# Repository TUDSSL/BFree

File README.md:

# BFree

This is the official public repository for a **battery-free** prototyping platform with [CircuitPython](https://circuitpython.org/) for the [Adafruit Metro M0 Express](https://www.adafruit.com/product/3505). This repository contains all the sources needed to get started using CircuitPython without any batteries!

## Project Overview

### Rationale
Batteries are bad for the environment, and many embedded applications do not rely on a constant flow of energy. However, just connecting an energy-harvesting source to a microcontroller does not fully solve the problem. Energy from harvested sources is not constant and maybe not enough to continuously run the device, so we have to buffer some energy (typically in a capacitor). When a certain amount of energy is collected, the system activates for some seconds.

It would be problematic if the program would start from the beginning every time the system restarts. Going into a sleep mode might also be problematic, as you never know when the energy returns.

**This work focuses on continuing a Python application where it left off when the system restarts after a power failure, called intermittent-computing**
We achieve this without any involvement from the user or any modifications to the Python code!

All the magic happens internally in our modified version of the CircuitPython interpreter ([added as a submodule in software/BFree-core](https://github.com/TUDSSL/BFree-core)), which works together with our [BFree shield](hardware/BFree-shield). Everything is entirely open-source and accessible through this GitHub repository.

The above figure presents: (A) the BFree hardware shield; (B) example Python code executed on the [Adafruit Metro M0 Express board](https://www.adafruit.com/product/3505) with the BFree shield; (C) the BFree shield with Adafruit Metro M0 Express board running a battery-free temperature measurement station; (D) the BFree system in the wild.

## How it works
For the user (maybe you!), the intermittent-computing aspect is entirely invisible. Internally, the modified CircuitPython interpreter communicates with the BFree shield and decides when to make a so-called "checkpoint." A checkpoint is a snapshot of the program at that point. When the system runs out of power and eventually starts back up, this is the point where the program will resume. The system always continues from the last *successful* checkpoint.
A checkpoint is created by sending the state of the interpreter (such as the current position in the program, the value of the variables, the state of the peripherals, etc.) to the BFree shield, which stores it in non-volatile memory (FRAM). For more details, please check out the complete paper [here](https://dl.acm.org/doi/abs/10.1145/3432191).

## Getting Started
To ditch all the batteries for your next CircuitPython project using BFree you need five things:
1. An [Adafruit Metro M0 Express board](https://www.adafruit.com/product/3505) 
2. A working [BFree shield](hardware/BFree-shield) programmed with the software in [software/nvm-controller](software/nvm-controller).
3. A build of the modified CircuitPyhton interpreter [BFree-core](https://github.com/TUDSSL/BFree-core))
4. An energy harvesting source (such as a small solar panel)
5. A buffer capacitor

The BFree shield is a simple shield-like PCB that mainly holds an MSP430 microcontroller onboard FRAM for non-volatile storage and energy harvesting circuitry. The modified CircuitPython interpreter (BFree-core) can be built and uploaded the same way as the vanilla CircuitPython. For this, we would like to refer you to the [excellent CircuitPython build instructions](https://learn.adafruit.com/building-circuitpython/build-circuitpython). Don't forget to use https://github.com/TUDSSL/BFree-core instead of https://github.com/adafruit/circuitpython.git

### Building the Hardware
All the EAGLE design files and a component list needed to build the BFree shield are availible in (hardware/BFree-shield)[hardware/BFree-shield].

### Building the BFree Shield Software
The [BFree shield sofware](https://github.com/TUDSSL/BFree/tree/main/software/nvm-controller) is build using [MSP430-gcc](https://www.ti.com/tool/MSP430-GCC-OPENSOURCE). To build it install the msp430-gcc toolchain in `/opt` or change the [msp430-toolchain.cmake](software/nvm-controller/msp430-toolchain.cmake) file to point to the toolchain.
Navigate to `software/nvm-controller/`; then it's as simple as running:
```
$ ./configure
$ cd build && make
```
And an elf file named `NVM-Controller.elf` will be generated in `software/nvm-controller/build/` which you can upload to the BFree shield using an MSP430 programmer, or using a MSP430 LaunchPad.

### Building the BFree Core Software
*Note: BFree Core has to be compiled using arm-gcc version 9! (not any higher version), this is due to a limitation in the original CircuitPython project*
To build the BFree version of CircuitPython, navigate to BFree-core and execute the following.
```
$ git submodule update --init --recursive
$ cd ports/atmel-samd
$ make BOARD=metro_m0_express
```
A `firmware.uf2` file will be generated in `ports/atmel-samd/build-metro_m0_express/` which can be uploaded to the Metro M0 Express board by [flashing it using the UF2 Bootloader](https://learn.adafruit.com/installing-circuitpython-on-samd21-boards/installing-circuitpython).

*Note that this is Beta software, so it's recommended to only flash BFree core if you also own a [J-Link](https://www.segger.com/products/debug-probes/j-link/models/j-link-edu/) programmer to recover the device if a bug occurs that prevents the system from entering the bootloader mode!*

## How to Operate BFree
**Just like a regular Metro M0 Express with CircuitPython!**

There is just one caveat when using peripheral devices (such as a sensor) that have a state that is reset when the system reboots. BFree can not know this, it will restore the peripheral interface (such as SPI), but it will not reinitialize the device.
Therefore the only change you need to make to your Python code *if* you have such a peripheral is to add the reinitialization just before the usage of the device. An example of this can be seen in [the LoRa application](https://github.com/TUDSSL/BFree/blob/a541a0d664f71f19883a6698cdb7067a455fbf71/software/applications-and-benchmarks/imwut-app-lora/main.py#L36)

## List of Known Issues
List of all known issues is listed in the [Issues](https://github.com/TUDSSL/BFree/issues) list of this project. If you found a bug or you would like to enhance BFree: [please contribute](#How-to-Contribute-to-this-Project) - we look forward to your pull requests!

## How to Contribute to this Project
We look forward to your contributions, improvements, additions and changes. Please follow the standard GitHub flow for code contributions. In macro terms this means the following.

1. Fork the master branch of this repository; make sure that your fork will be up to date with the latest master branch.
2. Create an issue here with a new feature or a bug report.
3. Perform changes on your local branch and push them to your forked clone.
4. Create a pull request referencing the issue it covers and wait for our response.

## Frequently Asked Questions

## How to Cite This Work

The results of this project have been published in a peer-reviewed academic publication (from which all technical figures in this file originate). Details of the publication are as follows.

* **Authors and the project team:** [Vito Kortbeek](https://www.vitokortbeek.com/), [Abu Bakar](http://www.abubakar.info/), [Stefany Cruz](https://www.linkedin.com/in/stefany-cruz-1386b4147/), [Kasim Sinan Yildirim](https://sinanyil81.github.io/), [Przemysław Pawełczak](http://www.pawelczak.net/), [Josiah Hester](https://josiahhester.com/)
* **Publication title:** _BFree: Enabling Battery-Free Sensor Prototyping with Python_
* **Pulication venue:** [Proceedings of the ACM on Interactive, Mobile, Wearable and Ubiquitous Technologies, Volume 4, Issue 4, December 2020](https://dl.acm.org/toc/imwut/2020/4/4) and [Proceedings of ACM UbiComp 2021](https://ubicomp.org/ubicomp2021/)
* [**Link to publication**](https://dl.acm.org/doi/abs/10.1145/3432191)
* [**Link to publication** (open access)](https://research.tudelft.nl/en/publications/bfree-enabling-battery-free-sensor-prototyping-with-python)
* [**Link to ACM UbiComp 2021 conference presentation video**](https://youtu.be/G-LVg8fWXtw)

To cite this publication please use the following BiBTeX entry.

```
@article{kortbeek:imwut:2020:bfree,
author = {Kortbeek, Vito and Bakar, Abu and Cruz, Stefany and Yildirim, Kasim Sinan and Pawe\l{}czak, Przemys\l{}aw and Hester, Josiah},
title = {BFree: Enabling Battery-Free Sensor Prototyping with Python},
journal = {Proc. ACM Interact. Mob. Wearable Ubiquitous Technol.},
year = {2020},
month = dec,
volume = {4},
number = {4},
articleno = {135},
numpages = {39},
publisher = {Association for Computing Machinery},
address = {New York, NY, USA},
url = {https://doi.org/10.1145/3432191}
}
```

## Acknowledgments

This research project was supported by [Netherlands Organisation for Scientific Research](https://www.nwo.nl/en), partly funded by the [Dutch Ministry of Economic Affairs and Climate Policy](https://www.government.nl/ministries/ministry-of-economic-affairs-and-climate-policy), through [TTW Perspective program ZERO (P15-06)](https://www.zero-program.nl/) within Project P4, and by the [National Science Foundation](https://www.nsf.org/) through grants [CNS-1850496](https://www.nsf.gov/awardsearch/showAward?AWD_ID=1850496), [CNS-2032408](https://www.nsf.gov/awardsearch/showAward?AWD_ID=2032408) and [CNS-2038853](https://www.nsf.gov/awardsearch/showAward?AWD_ID=2038853). Any opinions, findings, and conclusions or recommendations expressed in this material are those of the author(s) and do not necessarily reflect the views of the National Science Foundation.

BFree was designed at [Northwestern University](https://www.northwestern.edu) in the US and [Delft University of Technology](https://www.tudelft.nl) in the Netherlands, whose both support is also greatly acknowledged. 

## Copyright

Copyright (C) 2020-2021 TU Delft Embedded and Networked Systems Group/Sustainable Systems Laboratory.

MIT Licence. See [license](master/LICENSE) file for details.

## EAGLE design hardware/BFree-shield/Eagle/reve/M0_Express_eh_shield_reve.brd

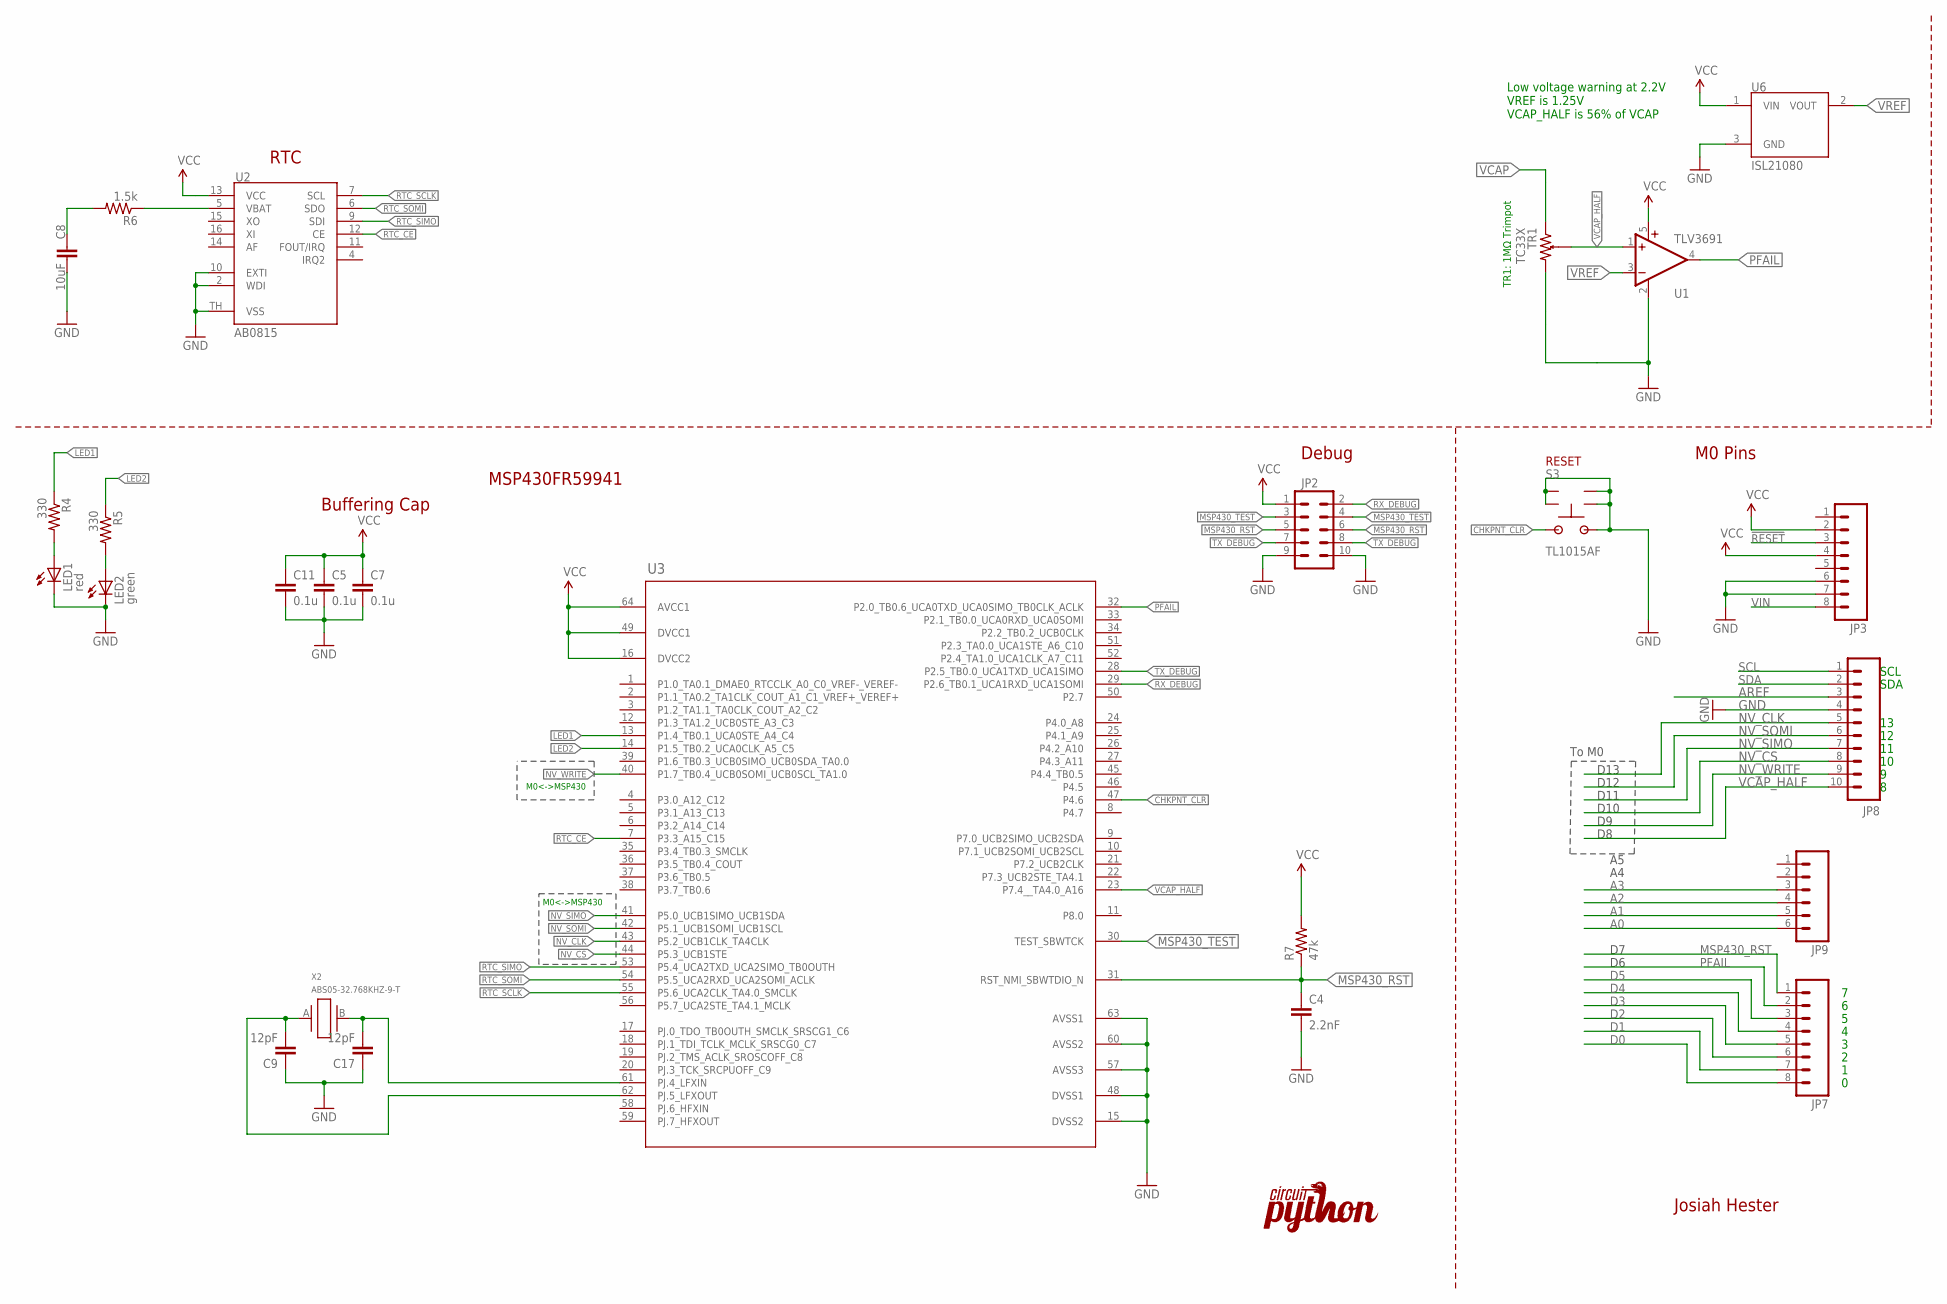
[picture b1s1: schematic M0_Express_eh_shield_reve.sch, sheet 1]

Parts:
C4: 2.2nF; 0603@1; MPN 06035C222KAT2A; DIGIKEY 478-1219-1-ND
C5, C7, C11: 0.1u; 0603@1; MPN CL10B104KO8NNNC; DIGIKEY 1276-1005-1-ND
C8: 10uF; 0805; DIGIKEY 1276-6456-1-ND
C9, C17: 12pF; 0603@1; MPN CL10C120JB8NNNC; DIGIKEY 1276-1254-1-ND
JP2: M05X21.27MM; 2X5_1.27MM; MPN 3220-10-0100-00; DIGIKEY 1175-1627-ND
JP3, JP7: M08LOCK; 1X08_LOCK
JP8: M10LOCK; 1X10_LOCK
JP9: M06LOCK; 1X06_LOCK
LED1: red; LED-0603
LED2: green; LED-0603
R4, R5: 330; 0603
R6: 1.5k; 0603; MPN CRG0603F1K5; DIGIKEY A121524CT-ND
R7: 47k; 0603; MPN CRCW060347K0JNEAC; DIGIKEY 541-4061-1-ND
S3: TL1015AF; TS1015; MPN TL1015AF160QG
TR1: TC33X; MPN TC33X-2-105E
U1: TLV3691; SC70-5; MPN TLV3691IDCKR; DIGIKEY 296-37910-1-ND
U2: AB0815; QFN16; MPN AB0815-T3
U3: MSP430FR5994IPM; PM0064A_N; DIGIKEY 296-45561-1-ND
U6: ISL21080; SOT-23; MPN ISL21080DIH312Z-TK; DIGIKEY ISL21080DIH312Z-TKTR-ND
U$1: LOGO; CIRCUITPYTHON-LOGO
X2: ABS05-32.768KHZ-9-T; ABS05; MPN ABS05-32.768KHZ-9-T

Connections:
!RESET: JP3.3
A0: JP9.6
A1: JP9.5
A2: JP9.4
A3: JP9.3
AREF: JP8.3
CHKPNT_CLR: S3.2, U3.47 (P4.6)
D0: JP7.8
D1: JP7.7
D2: JP7.6
D3: JP7.5
D4: JP7.4
D5: JP7.3
GND: C4.2, C5.2, C7.2, C8.2, C9.1, C11.2, C17.1, JP2.9, JP2.10, JP3.6, JP3.7, JP8.4, LED1.C, LED2.C, S3.1, S3.G1 (GND), S3.G2 (GND), S3.G3 (GND), S3.G4 (GND), TR1.2, U1.2 (GND), U2.2 (WDI), U2.10 (EXTI), U2.TH (VSS), U3.15 (DVSS2), U3.48 (DVSS1), U3.57 (AVSS3), U3.60 (AVSS2), U3.63 (AVSS1), U6.3 (GND); also elsewhere on the board
LED1: R4.1, U3.13 (P1.4_TB0.1_UCA0STE_A4_C4)
LED2: R5.1, U3.14 (P1.5_TB0.2_UCA0CLK_A5_C5)
MSP430_RST: C4.1, JP2.5, JP2.6, JP7.1, R7.1, U3.31 (RST_NMI_SBWTDIO_N)
MSP430_TEST: JP2.3, JP2.4, U3.30 (TEST_SBWTCK)
unnamed: R6.1, U2.5 (VBAT)
unnamed: C17.2, U3.61 (PJ.4_LFXIN), X2.B (2)
unnamed: C9.2, U3.62 (PJ.5_LFXOUT), X2.A (1)
unnamed: C8.1, R6.2
unnamed: LED1.A, R4.2
unnamed: LED2.A, R5.2
NV_CLK: JP8.5, U3.43 (P5.2_UCB1CLK_TA4CLK)
NV_CS: JP8.8, U3.44 (P5.3_UCB1STE)
NV_SIMO: JP8.7, U3.41 (P5.0_UCB1SIMO_UCB1SDA)
NV_SOMI: JP8.6, U3.42 (P5.1_UCB1SOMI_UCB1SCL)
NV_WRITE: JP8.9, U3.40 (P1.7_TB0.4_UCB0SOMI_UCB0SCL_TA1.0)
PFAIL: JP7.2, U1.4 (OUT), U3.32 (P2.0_TB0.6_UCA0TXD_UCA0SIMO_TB0CLK_ACLK)
RTC_CE: U2.12 (CE), U3.7 (P3.3_A15_C15)
RTC_SCLK: U2.7 (SCL), U3.55 (P5.6_UCA2CLK_TA4.0_SMCLK)
RTC_SIMO: U2.9 (SDI), U3.53 (P5.4_UCA2TXD_UCA2SIMO_TB0OUTH)
RTC_SOMI: U2.6 (SDO), U3.54 (P5.5_UCA2RXD_UCA2SOMI_ACLK)
RX_DEBUG: JP2.2, U3.29 (P2.6_TB0.1_UCA1RXD_UCA1SOMI)
SCL: JP8.1
SDA: JP8.2
TX_DEBUG: JP2.7, JP2.8, U3.28 (P2.5_TB0.0_UCA1TXD_UCA1SIMO)
VCAP: TR1.1; also elsewhere on the board
VCAP_HALF: JP8.10, TR1.W, U1.1 (+IN), U3.23 (P7.4__TA4.0_A16)
VCC: C5.1, C7.1, C11.1, JP2.1, JP3.4, R7.2, U1.5 (V+), U2.13 (VCC), U3.16 (DVCC2), U3.49 (DVCC1), U3.64 (AVCC1), U6.1 (VIN); also elsewhere on the board
VIN: JP3.8
VREF: U1.3 (-IN), U6.2 (VOUT); also elsewhere on the board

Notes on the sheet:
SDA
SCL
Josiah Hester
MSP430FR59941
M0 Pins
M0<->MSP430
D13
D12
D11
D10
RTC
To M0
Debug
Buffering Cap
RESET
Low voltage warning at 2.2V VREF is 1.25V VCAP_HALF is 56% of VCAP
TR1: 1MΩ Trimpot

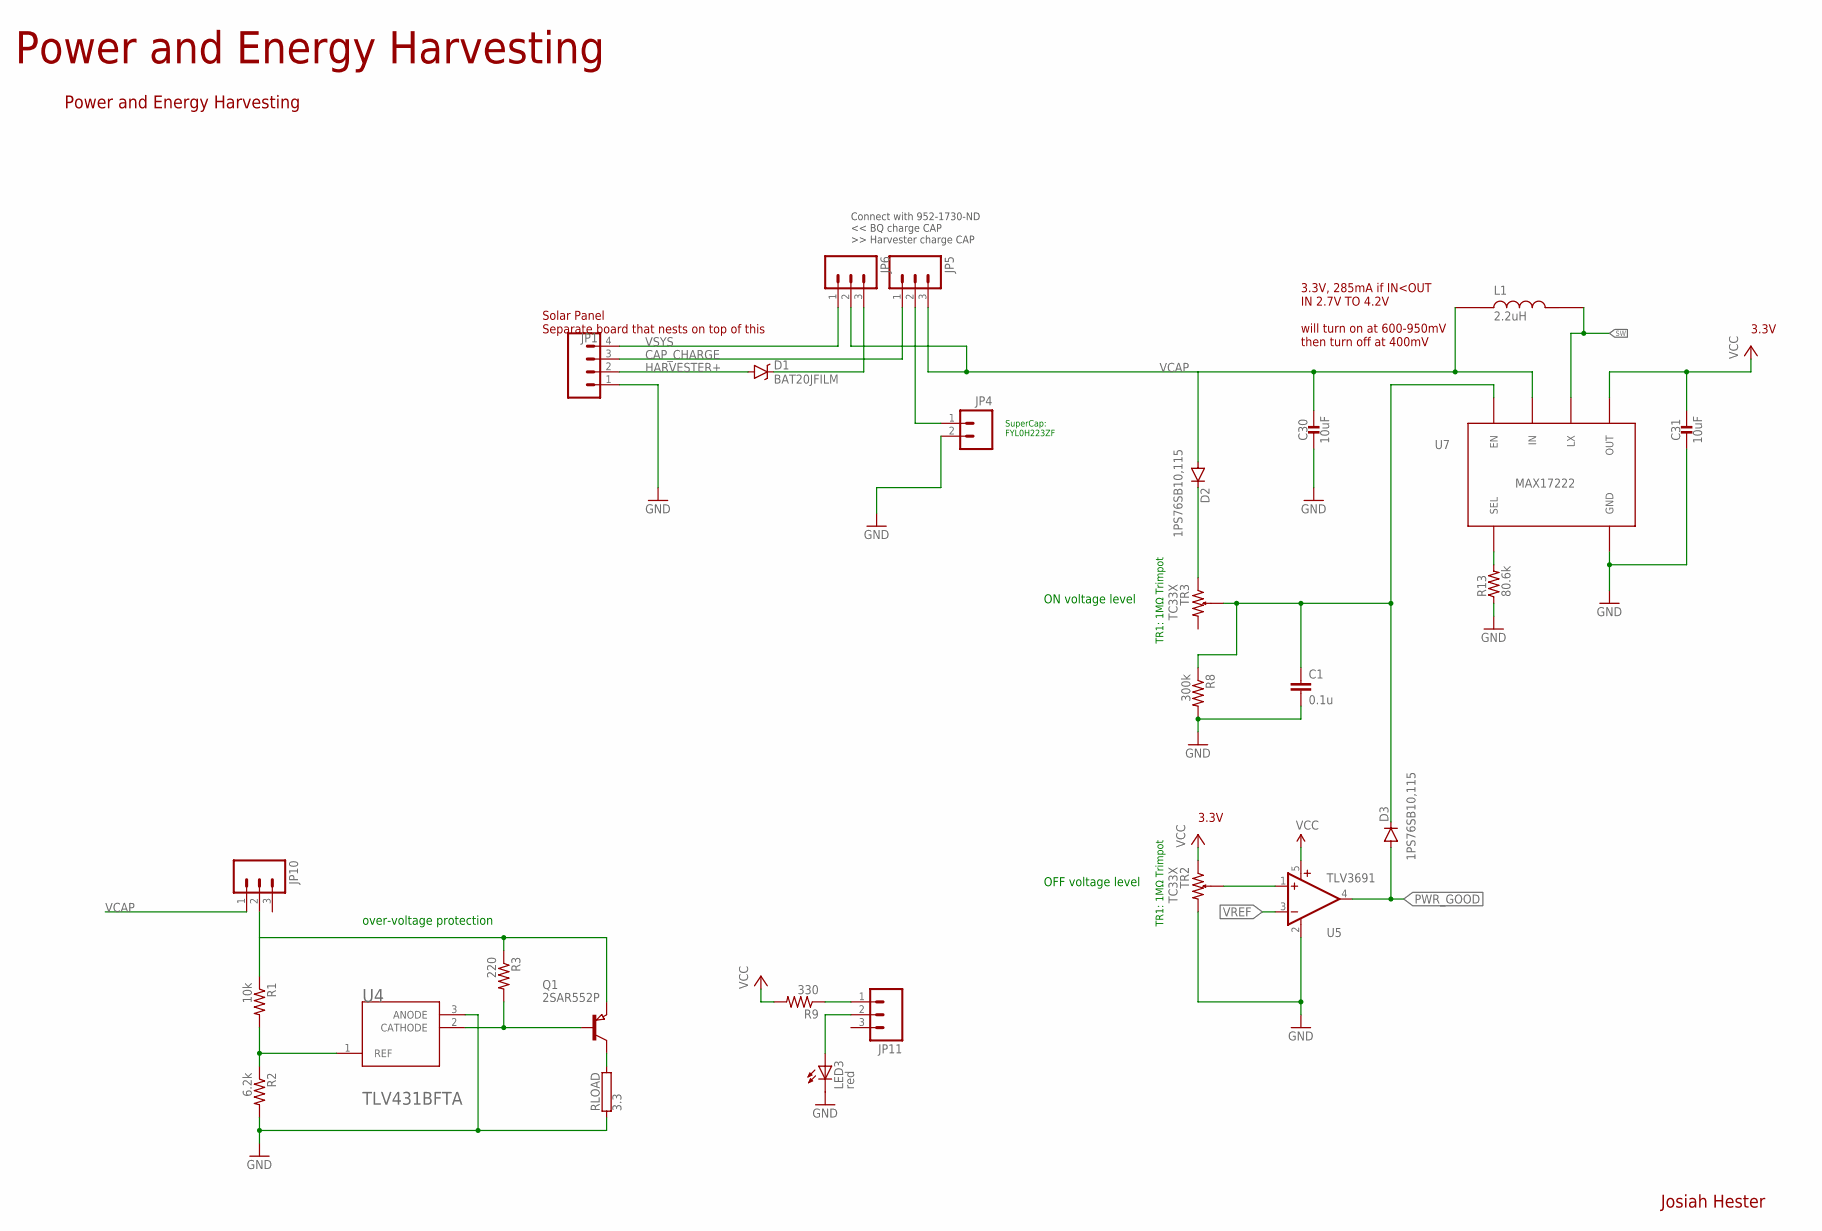
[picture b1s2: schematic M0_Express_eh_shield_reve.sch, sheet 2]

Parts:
C1: 0.1u; 0603@1; MPN CL10B104KO8NNNC; DIGIKEY 1276-1005-1-ND
C30, C31: 10uF; 0603_CAP; MPN GRM188R60J106ME47D; DIGIKEY 490-3896-1-ND
D1: BAT20JFILM; SOD-323; DIGIKEY NSR0530HT1GOSCT-ND
D2, D3: 1PS76SB10,115; SOD323-R
JP1: M04LOCK; 1X04_LOCK
JP4: M025MM; SCREWTERMINAL-5MM-2
JP5, JP6, JP10, JP11: M03; 1X03-1.27MM
L1: 2.2uH; IND_XFL4020-222MEB
LED3: red; LED-0603
Q1: 2SAR552P; SOT89
R1: 10k; 0603
R2: 6.2k; 0603
R3: 220; 0603
R8: 300k; 0603
R9: 330; 0603
R13: 80.6k; 0603-RES; MPN RC0603FR-0780K6L; DIGIKEY 311-80.6KHRCT-ND
RLOAD: 3.3; CA4060
TR2, TR3: TC33X; MPN TC33X-2-105E
U4: DIODES_TLV431BFTADIODES_TLV431BFTA_0_0; DIODES_TLV431BFTA_0
U5: TLV3691; SC70-5; MPN TLV3691IDCKR; DIGIKEY 296-37910-1-ND
U7: MAX17222; UDFN-6-MAXIM

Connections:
CAP_CHARGE: JP1.3, JP5.1
GND: C1.2, C30.2, C31.2, JP1.1, JP4.2, LED3.C, R2.2, R8.2, R13.1, RLOAD.1, TR2.2, U4.3 (ANODE), U5.2 (GND), U7.3 (GND); also elsewhere on the board
HARVESTER+: D1.A, JP1.2
unnamed: D1.C, JP6.3
unnamed: JP4.1, JP5.2
unnamed: R1.2, R2.1, U4.1 (REF)
unnamed: JP11.1, R9.1
unnamed: JP10.2, Q1.3 (E), R1.1, R3.1
unnamed: Q1.1 (B), R3.2, U4.2 (CATHODE)
unnamed: R13.2, U7.4 (SEL)
unnamed: Q1.2 (C), RLOAD.2
unnamed: C1.1, D3.C, R8.1, TR3.W, U7.6 (EN)
unnamed: D2.C, TR3.1
unnamed: JP11.2, LED3.A
ON_LVL: TR2.W, U5.1 (+IN)
PWR_GOOD: D3.A, U5.4 (OUT)
SW: L1.2, U7.2 (LX)
VCAP: C30.1, D2.A, JP5.3, JP6.2, JP10.1, L1.1, U7.5 (IN); also elsewhere on the board
VCC: C31.1, R9.2, TR2.1, U5.5 (V+), U7.1 (OUT); also elsewhere on the board
VREF: U5.3 (-IN); also elsewhere on the board
VSYS: JP1.4, JP6.1

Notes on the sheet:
Power and Energy Harvesting
SuperCap: FYL0H223ZF
Josiah Hester
3.3V
3.3V, 285mA if IN<OUT IN 2.7V TO 4.2V will turn on at 600-950mV then turn off at 400mV
Solar Panel Separate board that nests on top of this
Connect with 952-1730-ND << BQ charge CAP >> Harvester charge CAP
over-voltage protection
TR1: 1MΩ Trimpot
ON voltage level
OFF voltage level

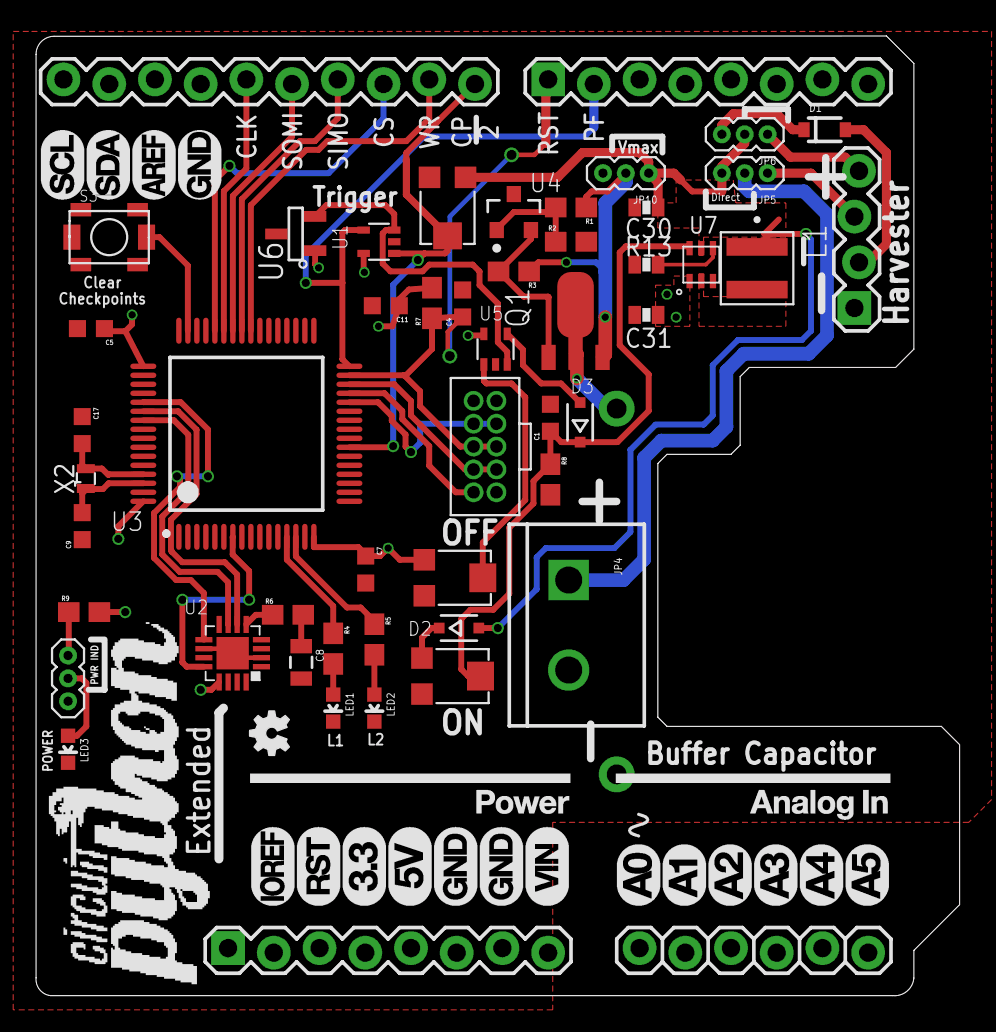
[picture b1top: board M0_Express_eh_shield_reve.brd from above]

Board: 2 copper layers, 51.3 x 53.3 mm, 54 parts (1 on the bottom side), 45 nets.

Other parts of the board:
U$2: OSHW-LOGO-MINI

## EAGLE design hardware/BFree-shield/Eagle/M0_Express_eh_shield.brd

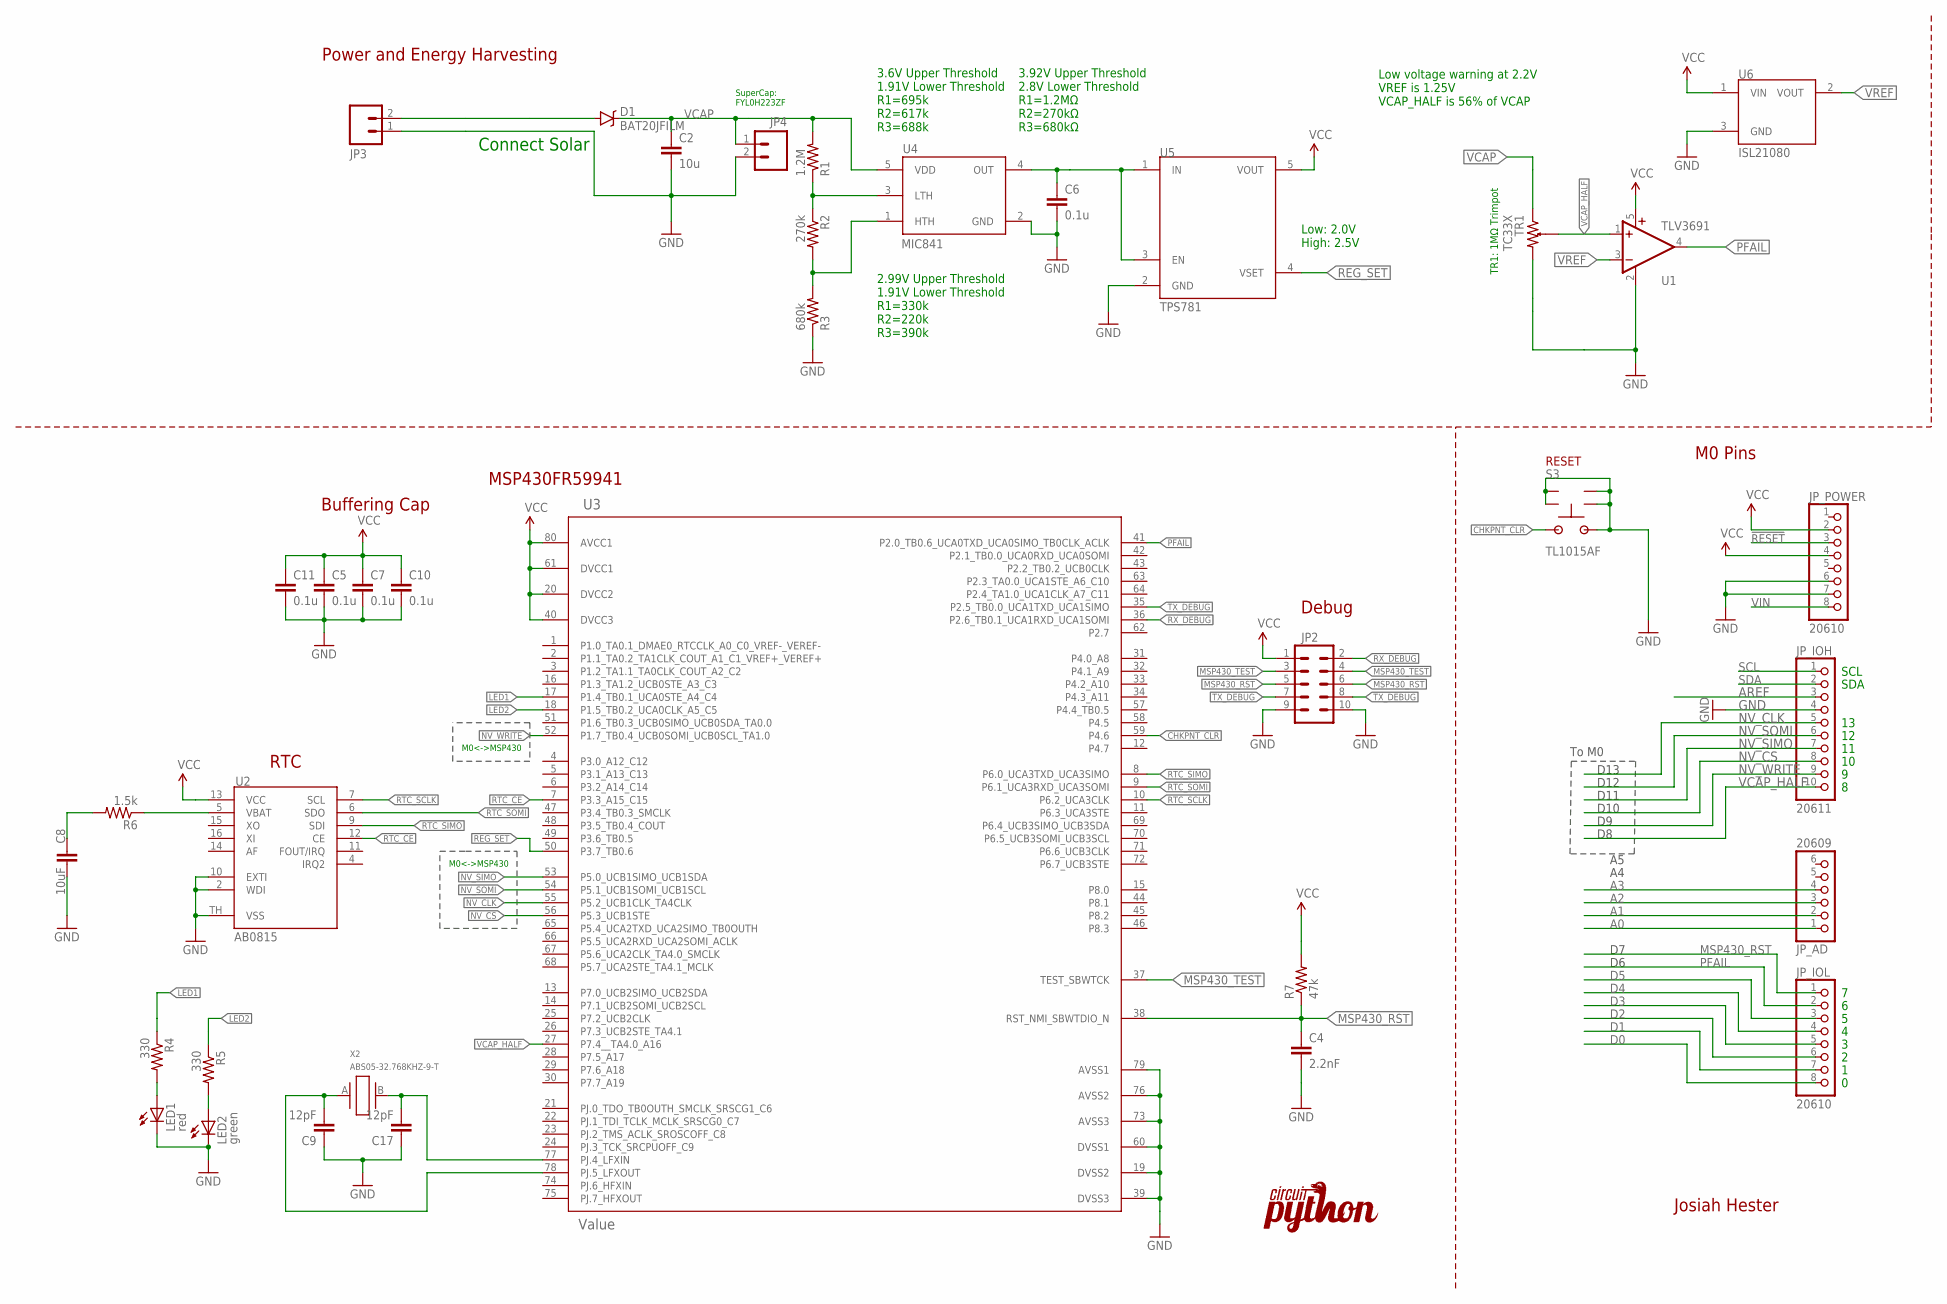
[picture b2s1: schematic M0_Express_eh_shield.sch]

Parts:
C2: 10u; 0805; DIGIKEY 1276-6456-1-ND
C4: 2.2nF; 0603@1; MPN 06035C222KAT2A; DIGIKEY 478-1219-1-ND
C5, C6, C7, C10, C11: 0.1u; 0603@1; MPN CL10B104KO8NNNC; DIGIKEY 1276-1005-1-ND
C8: 10uF; 0805; DIGIKEY 1276-6456-1-ND
C9, C17: 12pF; 0603@1; MPN CL10C120JB8NNNC; DIGIKEY 1276-1254-1-ND
D1: BAT20JFILM; SOD-323; DIGIKEY NSR0530HT1GOSCT-ND
JP2: M05X21.27MM; 2X5_1.27MM; MPN 3220-10-0100-00; DIGIKEY 1175-1627-ND
JP3, JP4: M025MM; SCREWTERMINAL-5MM-2
JP_AD: 20609; 1X06_OVALWAVE
JP_IOH: 20611; 1X10_OVALWAVE
JP_IOL: 20610; 1X08_OVALWAVE
JP_POWER: 20610; 1X08_OVALWAVE
LED1: red; LED-0603
LED2: green; LED-0603
R1: 1.2M; 0603; MPN RC0603JR-071M2L; DIGIKEY 311-1.2MGRCT-ND
R2: 270k; 0603; MPN RK73B1JTTD274J; DIGIKEY 2019-RK73B1JTTD274JCT-ND
R3: 680k; 0603; MPN RMCF0603FT680K; DIGIKEY RMCF0603FT680KCT-ND
R4, R5: 330; 0603
R6: 1.5k; 0603; MPN CRG0603F1K5; DIGIKEY A121524CT-ND
R7: 47k; 0603; MPN CRCW060347K0JNEAC; DIGIKEY 541-4061-1-ND
S3: TL1015AF; TS1015; MPN TL1015AF160QG
TR1: TC33X; MPN TC33X-2-105E
U1: TLV3691; SC70-5; MPN TLV3691IDCKR; DIGIKEY 296-37910-1-ND
U2: AB0815; QFN16; MPN AB0815-T3
U3: Value; PN0080A_N; DIGIKEY 296-45561-1-ND
U4: MIC841; SC70-5; MPN MIC841HYC5-TR; DIGIKEY 576-2923-1-ND
U5: TPS781; DCK_R-PDSO-G5; MPN TPS781250200DDCR; DIGIKEY 296-29966-1-ND
U6: ISL21080; SOT-23; MPN ISL21080DIH312Z-TK; DIGIKEY ISL21080DIH312Z-TKTR-ND
U$1: LOGO; CIRCUITPYTHON-LOGO
X2: ABS05-32.768KHZ-9-T; ABS05; MPN ABS05-32.768KHZ-9-T

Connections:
!RESET: JP_POWER.3
A0: JP_AD.1
A1: JP_AD.2
A2: JP_AD.3
A3: JP_AD.4
AREF: JP_IOH.3
CHKPNT_CLR: S3.2, U3.59 (P4.6)
D0: JP_IOL.8
D1: JP_IOL.7
D2: JP_IOL.6
D3: JP_IOL.5
D4: JP_IOL.4
D5: JP_IOL.3
GND: C2.2, C4.2, C5.2, C6.2, C7.2, C8.2, C9.1, C10.2, C11.2, C17.1, JP2.9, JP2.10, JP3.1, JP4.2, JP_IOH.4, JP_POWER.6, JP_POWER.7, LED1.C, LED2.C, R3.1, S3.1, S3.G1 (GND), S3.G2 (GND), S3.G3 (GND), S3.G4 (GND), TR1.2, U1.2 (GND), U2.2 (WDI), U2.10 (EXTI), U2.TH (VSS), U3.19 (DVSS2), U3.39 (DVSS3), U3.60 (DVSS1), U3.73 (AVSS3), U3.76 (AVSS2), U3.79 (AVSS1), U4.2 (GND), U5.2 (GND), U6.3 (GND)
LED1: R4.1, U3.17 (P1.4_TB0.1_UCA0STE_A4_C4)
LED2: R5.1, U3.18 (P1.5_TB0.2_UCA0CLK_A5_C5)
MSP430_RST: C4.1, JP2.5, JP2.6, JP_IOL.1, R7.1, U3.38 (RST_NMI_SBWTDIO_N)
MSP430_TEST: JP2.3, JP2.4, U3.37 (TEST_SBWTCK)
unnamed: D1.A, JP3.2
unnamed: R1.1, R2.1, U4.3 (LTH)
unnamed: R2.2, R3.2, U4.1 (HTH)
unnamed: R6.1, U2.5 (VBAT)
unnamed: C17.2, U3.77 (PJ.4_LFXIN), X2.B (2)
unnamed: C9.2, U3.78 (PJ.5_LFXOUT), X2.A (1)
unnamed: C6.1, U4.4 (OUT), U5.1 (IN), U5.3 (EN)
unnamed: C8.1, R6.2
unnamed: LED1.A, R4.2
unnamed: LED2.A, R5.2
NV_CLK: JP_IOH.5, U3.55 (P5.2_UCB1CLK_TA4CLK)
NV_CS: JP_IOH.8, U3.56 (P5.3_UCB1STE)
NV_SIMO: JP_IOH.7, U3.53 (P5.0_UCB1SIMO_UCB1SDA)
NV_SOMI: JP_IOH.6, U3.54 (P5.1_UCB1SOMI_UCB1SCL)
NV_WRITE: JP_IOH.9, U3.52 (P1.7_TB0.4_UCB0SOMI_UCB0SCL_TA1.0)
PFAIL: JP_IOL.2, U1.4 (OUT), U3.41 (P2.0_TB0.6_UCA0TXD_UCA0SIMO_TB0CLK_ACLK)
REG_SET: U3.50 (P3.7_TB0.6), U5.4 (VSET)
RTC_CE: U2.12 (CE), U3.7 (P3.3_A15_C15)
RTC_SCLK: U2.7 (SCL), U3.10 (P6.2_UCA3CLK)
RTC_SIMO: U2.9 (SDI), U3.8 (P6.0_UCA3TXD_UCA3SIMO)
RTC_SOMI: U2.6 (SDO), U3.9 (P6.1_UCA3RXD_UCA3SOMI)
RX_DEBUG: JP2.2, U3.36 (P2.6_TB0.1_UCA1RXD_UCA1SOMI)
SCL: JP_IOH.1
SDA: JP_IOH.2
TX_DEBUG: JP2.7, JP2.8, U3.35 (P2.5_TB0.0_UCA1TXD_UCA1SIMO)
VCAP: C2.1, D1.C, JP4.1, R1.2, TR1.1, U4.5 (VDD)
VCAP_HALF: JP_IOH.10, TR1.W, U1.1 (+IN), U3.27 (P7.4__TA4.0_A16)
VCC: C5.1, C7.1, C10.1, C11.1, JP2.1, JP_POWER.2, JP_POWER.4, R7.2, U1.5 (V+), U2.13 (VCC), U3.20 (DVCC2), U3.40 (DVCC3), U3.61 (DVCC1), U3.80 (AVCC1), U5.5 (VOUT), U6.1 (VIN)
VIN: JP_POWER.8
VREF: U1.3 (-IN), U6.2 (VOUT)

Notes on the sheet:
SDA
SCL
Josiah Hester
MSP430FR59941
Power and Energy Harvesting
M0 Pins
2.99V Upper Threshold 1.91V Lower Threshold R1=330k R2=220k R3=390k
Low: 2.0V High: 2.5V
M0<->MSP430
D13
D12
D11
D10
RTC
To M0
Connect Solar
Debug
Buffering Cap
3.6V Upper Threshold 1.91V Lower Threshold R1=695k R2=617k R3=688k
Low voltage warning at 2.2V VREF is 1.25V VCAP_HALF is 56% of VCAP
SuperCap: FYL0H223ZF
RESET
TR1: 1MΩ Trimpot
3.92V Upper Threshold 2.8V Lower Threshold R1=1.2MΩ R2=270kΩ R3=680kΩ

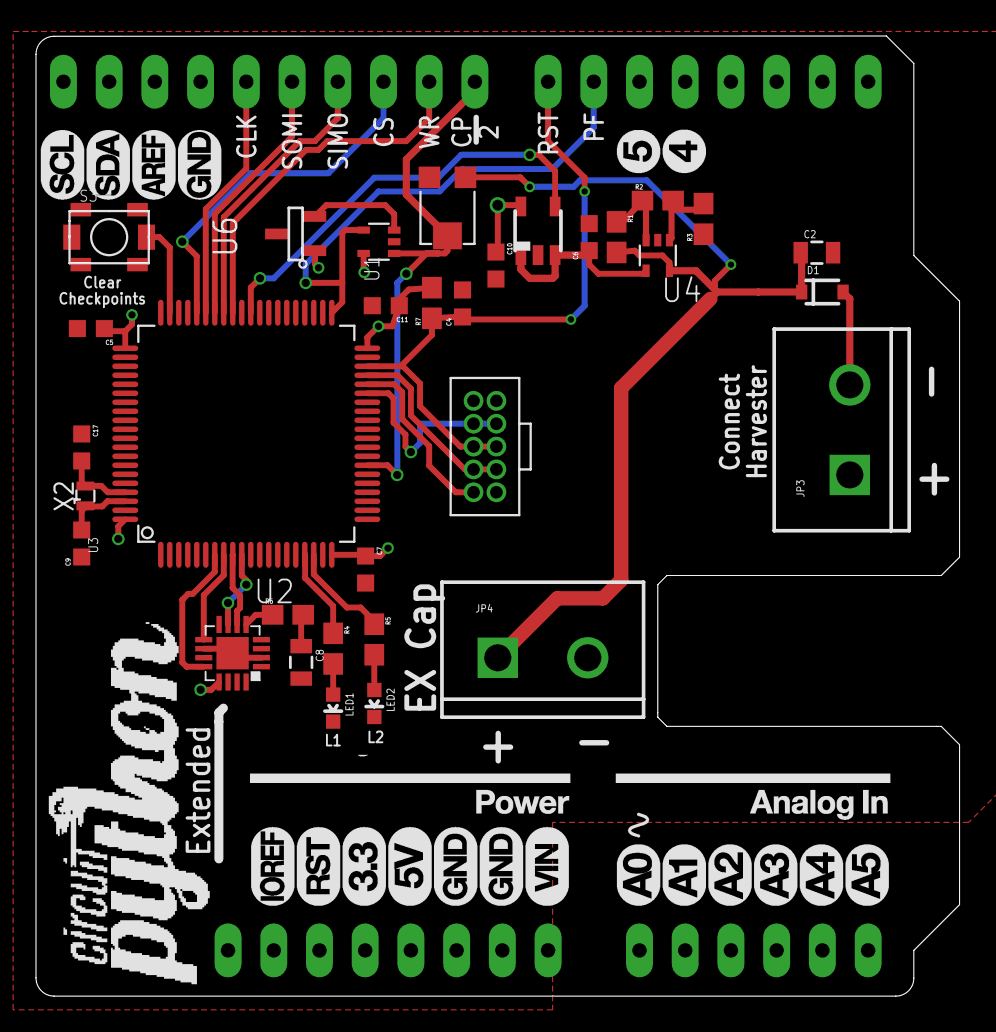
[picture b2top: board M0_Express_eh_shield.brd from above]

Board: 2 copper layers, 51.3 x 53.3 mm, 37 parts (0 on the bottom side), 33 nets.

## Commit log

2020-11-06 Create README.md
    Initial push of README
2020-11-06 Create LICENSE
    Created license
2020-11-09 Update README.md
    Section How to Cite This Work expanded
2020-11-09 Update README.md
    Added List of Known Issues section
2020-11-09 Create tudelft_logo.png
    tudelft_logo.png added
2020-11-09 Add files via upload
    tudelft_logo.png revised
2020-11-09 Add files via upload
    northwestern logo added
2020-11-09 Add files via upload
    overview figure added
2020-11-09 Update README.md
    Adding a Project Overview text and TUD/northwestern figures
2020-11-09 Update README.md
    Master changed into main
2020-11-09 Add files via upload
    BFree overview image added
2020-11-09 Update README.md
    Review of text in Project Overview section
2020-11-09 Update README.md
    Placeholder for Table of Contents
2020-11-09 Delete bfree-overview.jpg
    deleted bfree-overview.jpg from main
2020-11-09 Update README.md
    Revision of file header
2021-04-08 Add BFree-core submodule
2021-04-08 Make BFree-core submodule track the main branch
2021-04-08 Add BFree-shield code
2021-04-08 Add applications and benchmarks
2021-04-08 Add hardware files
2021-04-08 Add the C benchmark code
2021-04-08 Add the measurements
2021-04-08 Add user-study
2021-04-08 Remove random hidden file
2021-05-30 Added initial version of neural network
2021-06-17 Cleaned up code, added documentation, added model build script
2021-06-17 Improved readme
2021-06-19 Cleanup, improved comments and documentation, moved and renamed files.
2021-06-19 Ran formatter on all files
2021-06-19 Fixed some docstrings
2021-06-19 Further directory cleanup, added directory for compiled library files.
2021-06-19 improved imports, fixed bug with optional parameter in demo, updated notebook
2021-06-24 Small fix & added problem to readme
2021-06-24 Updated circuitpython version, added compiled .mpy files.
2021-06-24 Rescale output to remove overshoot, updated README.md
2021-07-02 Improved documentation, removed unnecessary fields and model, added Mu image.
2021-07-02 Added Mu screenshot to readme.
2021-07-02 Added forgotten licence to layer.py and net.py
2021-07-02 Small change in documentation.
2021-07-06 Added copyright to models.ipynb, small changes in readme
2021-07-07 Removed unnecessary newlines in readme
2021-09-16 [BFree-core] Update submodule
2022-01-27 Add Weather Station example project
2022-01-27 Fix spelling for the Weather Station example
2022-01-27 Update Weather Station example README
2022-01-27 Add images to Weather Station example README
2022-01-27 Update Weather Station receiver code
2022-01-28 [Weater Station] Remove outdated comment
2022-01-28 [Weater Station] Add BFree shield pre-compiled firmware
2022-01-28 [Weather Station] Fix major spelling mistake
2022-06-03 Add a PC GUI to live plot weather station data
2022-06-03 New hardware `reve` revision for the BFree shield (skipping `revd`)
    * Updated boost converter design
    * Configurable on/off levels for the system
    * Over voltage protection for harvesting sources above 3 volt
    * Changed MSP430 to another model due to the chip shortage
    The same MSP .elf can be used, it's only a different package.
    This is also why `revd` is skipped. As this contained the same changes
2023-03-09 Update README.md
    Typo

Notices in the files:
parts and their libraries:
microbuilder: This work is placed in the public domain, and may be freely used for commercial and non-commercial work with the following conditions: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
SparkFun-Capacitors: Licensing: Creative Commons ShareAlike 4.0 International - https://creativecommons.org/licenses/by-sa/4.0
